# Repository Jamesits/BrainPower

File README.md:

# BrainPower

PCI express x1 (full-height, half-length) socket to 12V DC adapter with specific MikroTik router mounting holes.

## Shit Advertisement

BrainPower adds true **hardware-level NFV functionality** for your ~~servers~~ private cloud, making it more suitable for **IoT**, **edge computing**, **fog computing** and branch office deployment.

BrainPower brings the only **hardware-level network redundancy option** on the market for ~~single server deployment~~ economic hyperconverged solution as long as your enclosure is large enough. 

BrainPower integrates with your current and future OOB management systems and allows **next-generation SD-WAN** based management network. 

BrainPower enables seamless transition of your legacy network architecture into a more modern, **hybrid cloud architecture**, bringing new possibilities for the smallest number of enclosures.

## Rendered Graphics

Note: this is a rendered version of [BrainPower v0.3](https://github.com/Jamesits/BrainPower/commit/e29cd585c712ce8d517ac3b23541380fda902caa) and is subject to change. It does not represent the final product.

For actual photos, see:

* [Version 0.1](https://github.com/Jamesits/BrainPower/wiki/Version-0.1)
* [Version 0.2](https://github.com/Jamesits/BrainPower/wiki/Version-0.2)

## Compatibility

### DC powering options

* 5.5*2.1mm Barrel Jack (compatible with the most common unbranded ones like [this](https://www.adafruit.com/product/373))
* [PHOENIX CONTACT MCV 1,5_2-G-5.08](https://www.phoenixcontact.com/online/portal/us?uri=pxc-oc-itemdetail:pid=1836299&library=usen&tab=1) (intended for wire soldering)

### Mounting hole compatibility

It is compatible with the following MikroTik routers:

**RB750 Series**

* RB750r1/r2/Gr2/Gr3
* RB760iGS
* hAP lite
* hAP AC lite
* hAP AC²

**RB450 Series**

* RB450x2
* RB450Gx2
* RB450Gx4
* RB850Gx2

## Production Guide

### Ordering

For stable or testing releases, you can go to [releases](https://github.com/Jamesits/BrainPower/releases) to download an gerber files archive. Most PCB manufacture sites accept this format.

For development version, you can use the open-source [KiCAD](http://www.kicad-pcb.org/) to open the project file located in the `BrainPower` sub-folder and plot the gerber files.

### Notes when ordering PCB

* PCB thickness: 1.6mm
* 45° chamfered border for gold fingers

### Assembling

Mounting holes for the router are ⌀3.7mm holes, you can use M3 hexagonal column and screws. Mount the router on the B side of the PCB (the side with the "KICK" characters) to comply with PCI express standard; mounting backwards also works with some caveats (reads: we never tested it).

### PCI express I/O Bracket

The PCI express I/O bracket mounting holes are of the same size and position as in *Figure 6-1* and *Figure 6-9*, [*PCI Express® Card Electromechanical Specification Revision 2.0*](https://members.pcisig.com/wg/PCI-SIG/document/download/8285). You can use the brackets from common SAS cards (e.g. LSI SAS9217-8i). 

## Acknowledgement

The PCI express board shape is from [x1 Desktop / Server Rec. Length Card](https://designcontent.live.altium.com/TemplateDesigns/PCI%20Express#TemplateDesignDetail/PDE-0001-00054) and converted with [altium2kicad](https://github.com/thesourcerer8/altium2kicad). Shapes and characters are converted using [svg2shenzhen](https://github.com/badgeek/svg2shenzhen).

The board's name and the fonts came from [NOMA - Brain Power](https://www.youtube.com/watch?v=h-mUGj41hWA) by Martin.

The following people provided assistance and help during the making of this product:

* [Wencey Wang](https://github.com/WenceyWang)
* [LTY](https://github.com/lty1993)
* [Star Brilliant](https://github.com/m13253)
* [Jeremy Wu](https://github.com/jemerywudev)

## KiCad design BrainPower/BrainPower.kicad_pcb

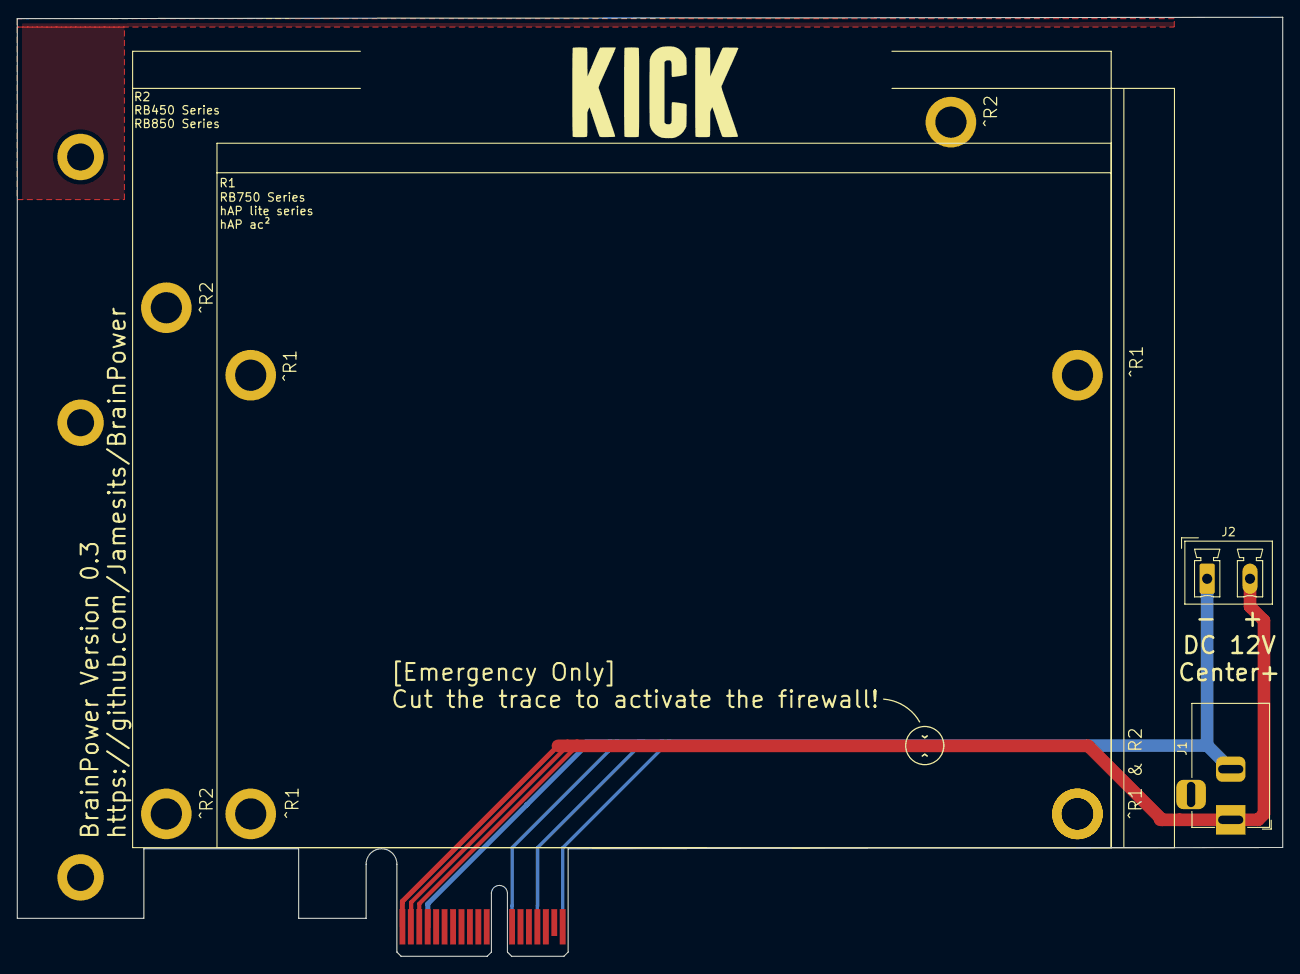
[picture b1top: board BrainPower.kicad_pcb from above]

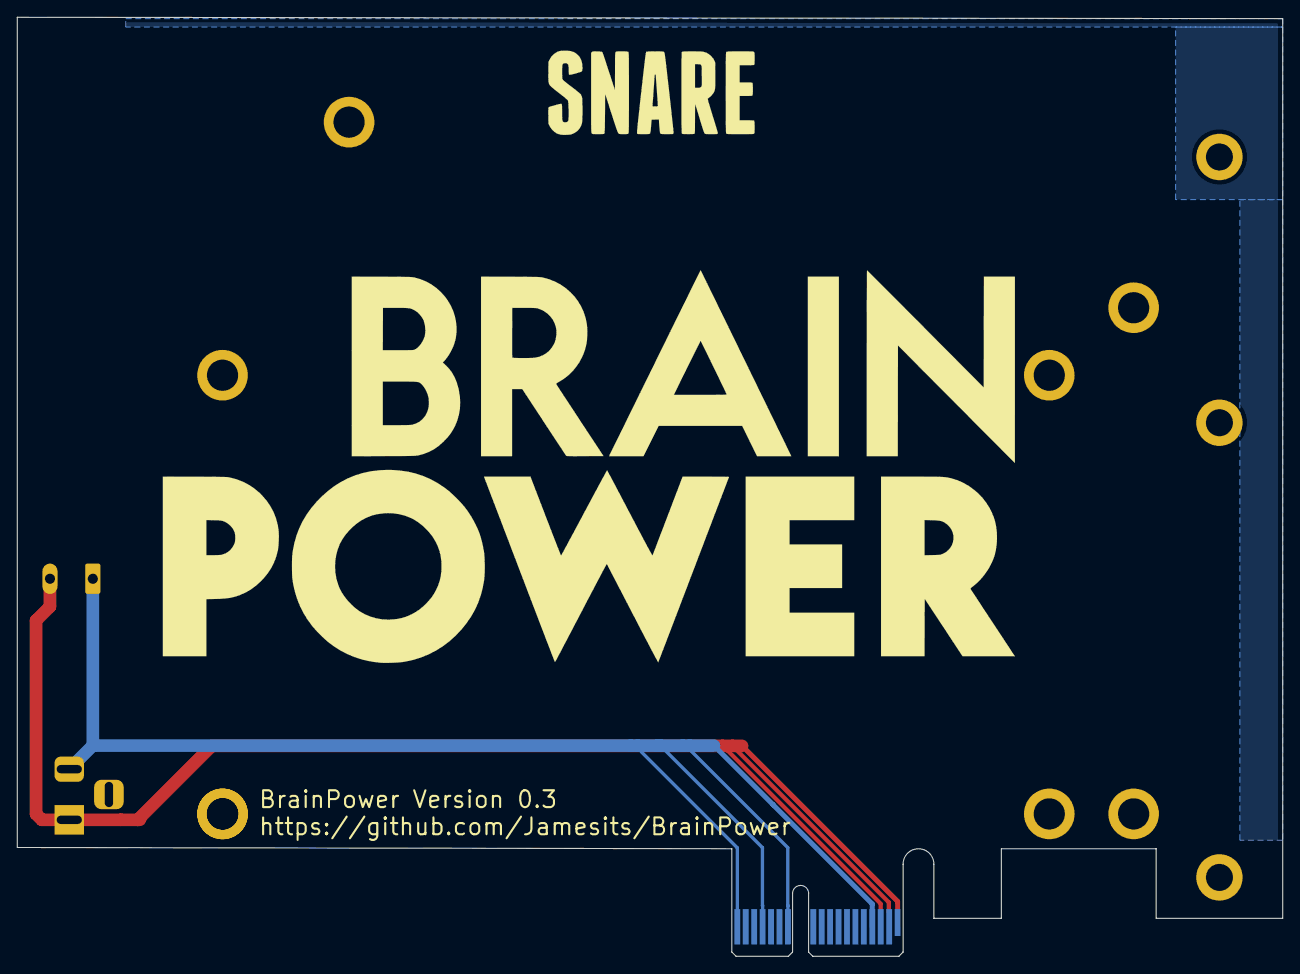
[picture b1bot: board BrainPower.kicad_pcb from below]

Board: 2 copper layers, 150.0 x 111.3 mm, 11 parts (2 on the bottom side), 2 nets.

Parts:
J1: BarrelJack_Horizontal
J2: PhoenixContact_MCV_1,5_2-G-5.08_1x02_P5.08mm_Vert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; PhoenixContact_MCV_1,5_2-G-5.08_1x02_P5.08mm_Vertical
MH1, MH2, MH3: MountingHole_3.2mm_M3_ISO14580_Pad
P1: Golden finger, PCIeX1, Dual, Opposite, Pitch 1mm,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; PCIeX1-GF-2D-1000-1K-O36
R1: RB750Gr3
R2: RB450Gx4
Ref**: Val**; BRAIN POWER
Ref**#2: Val**; KICK
Ref**#3: Val**; SNARE

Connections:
+12V: J1.1, J2.2, P1.B1, P1.B2, P1.B3
GND: J1.2, J2.1, P1.A4, P1.A12, P1.A15, P1.A18

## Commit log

2019-10-15 RB750Gr3 version
2019-10-15 update gerber files
2019-10-15 add README
2019-10-15 add optional soldering pads for 12V
2019-10-16 remove unused footprints
2019-10-16 added compatibility for RB450 series
2019-10-16 removed redundant keepout zone on copper
2019-10-16 add comments for CNC
2019-10-16 fix footprint positioning
2019-10-16 remove redundant silkscreen
2019-10-16 adjust silkscreen
2019-10-16 move files around
2019-10-16 thicker wire
2019-10-16 normalize board edge
2019-10-19 update license
2019-10-19 remove mikrotik pictures from the repo for copyright issues
2019-10-19 test funding
2019-10-19 fix mounting hole ordering
2019-10-19 add github link on the back of the board
2019-10-19 v0.2 test production
2019-10-23 add some silkscreen words
2019-10-23 update rendered pics commit link
2019-10-23 add wiki links
2019-11-07 add compatibility with low profile PCI express I/O brackets
2020-02-15 update v0.3 rendered photo
2020-02-15 add acknowledgement to svg2shenzhen
